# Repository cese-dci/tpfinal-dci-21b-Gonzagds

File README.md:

## Trabajo práctico final de la asignatura DCI ##
Este repositorio contiene el trabajo práctico final para la asignatura de Diseño de Circuitos Impresos de la carrera de posgrado de FIUBA.

* Autor: Gonzalo Daniel Sanchez
* Título corto del trabajo:  Programador y debugger para módulos ESP-32
* Descripción: Esta placa hace uso de un conversor USB a UART/JTAG/I2C/SPI de la empresa FTDI para implementar un grabador y debugger para módulos y kits de desarrollo de la empresa Espresiff. La placa tiene un conector para usar de grabador y otro conector para usa de debugger.
Para el grabador se configura uno de los puertos del  conversor FTDI como un puerto UART y se conectan las señales de RX y TX a la UART del módulo ESP32. Las señales de CTS y RTS se utilizan para comandar las señales de reset y programación del módulo. Esta interfaz también se puede utilizar como simple conversor USB a UART para interactuar con la consola del modulo.
El otro puerto del conversor FTDI se configura como una interfaz JTAG y se conecta directamente a las señales de JTAG del módulo Espressif.

## Licencia de este trabajo ##
XXXMENCIONAR ACÁ LA LICENCIAXXX (Editar este párrafo) 
Y además colcar el archivo de texto de la misma en el directorio raíz.
Para este TP se pide que la licencia sea de hardware abierto.
Ver la sección "What license should I use?": https://www.oshwa.org/faq/

## Estructura del TP FINAL ##

Se propone y se pide utilizar la siguiente estructura.

* doc: Toda la información sobre el circuito, principalmente de autoría o procesamiento propio. Por ejemplo:
  * Notas de ingeniería propias.
  * Notas de aplicación propias.
  * Estudios previos, estado del arte, resumen de las investigaciones.
  * Notas con cálculos.
  * Dibujos adicionales.
  * Fotos de los prototipos.
  * Presupuestos, cotizaciones.
* info: Toda la iformación recolectada, principalmente de terceros, como por ejemplo:
  * Hojas de datos.
  * Notas de aplicación.
  * Info de productos comerciales.
  * Info en internet.
* pcb: Archivos de diseño esquemático y pcb.

Dependiendo la magnitud del proyecto, tendremos más o menos información en estos directorios. 
Revisar los README.md en cada directorio para conocer las pautas de cada uno para este TP.

NOTA: El alumno puede y debe borrar de este archivo todo lo que considere necesario, por ejemplo las aclaraciones del docente y esta misma nota.

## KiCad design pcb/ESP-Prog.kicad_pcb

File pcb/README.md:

## Archivos Kicad ##

En este directorio debería ir:

* Archivos de proyecto.
* Esquemático.
* PCB.
* Modelos  3D.
* Bibliotecas de símbolos y huellas externas (si son necesarios).

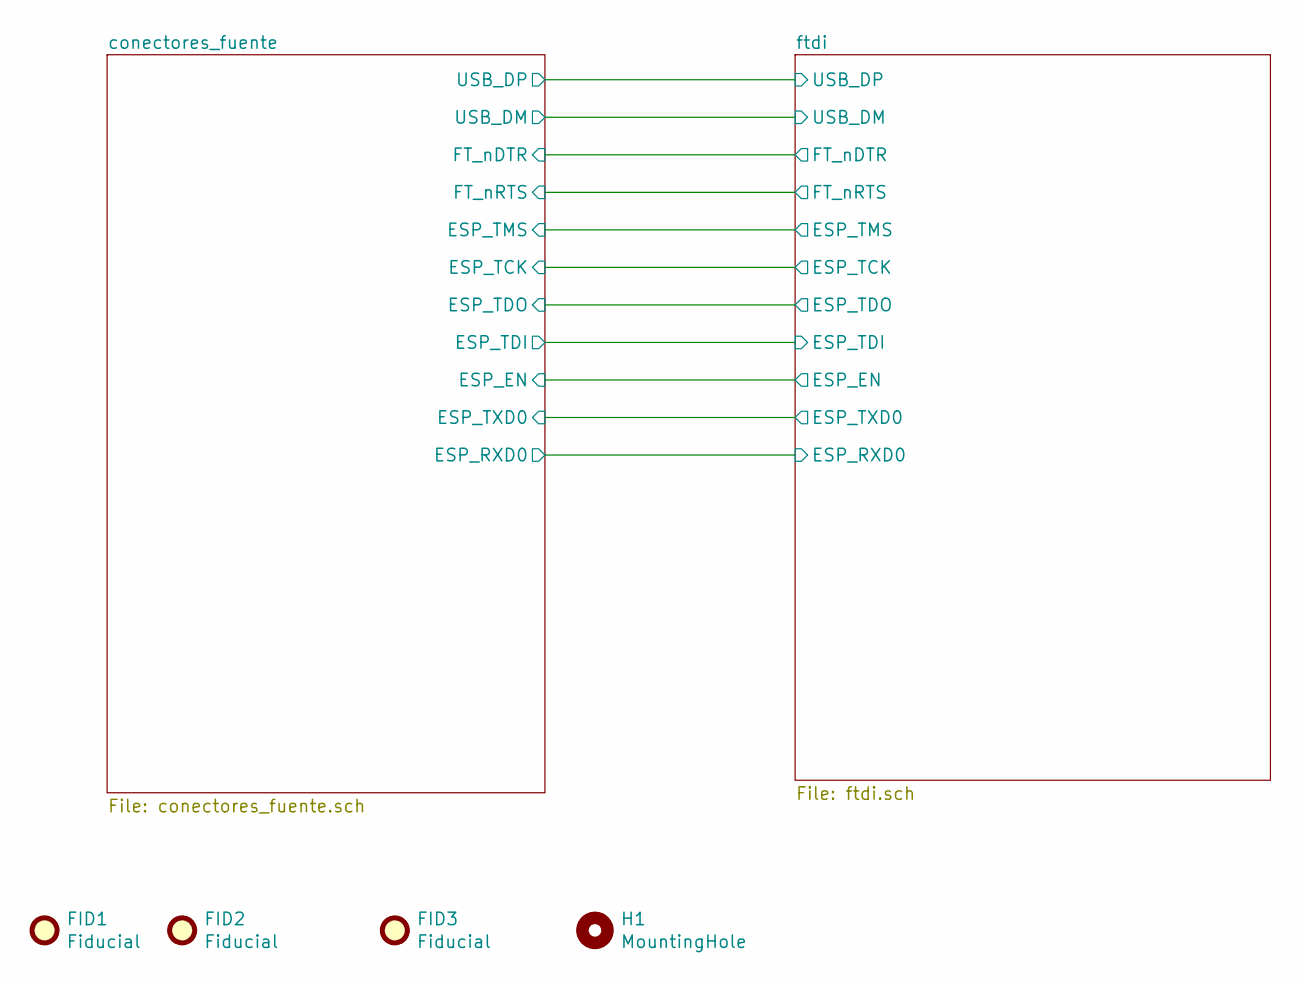
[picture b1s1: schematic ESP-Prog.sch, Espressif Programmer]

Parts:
FID1, FID2, FID3: Fiducial; Fiducial_0.5mm_Mask1mm
H1: MountingHole; MountingHole_2.5mm

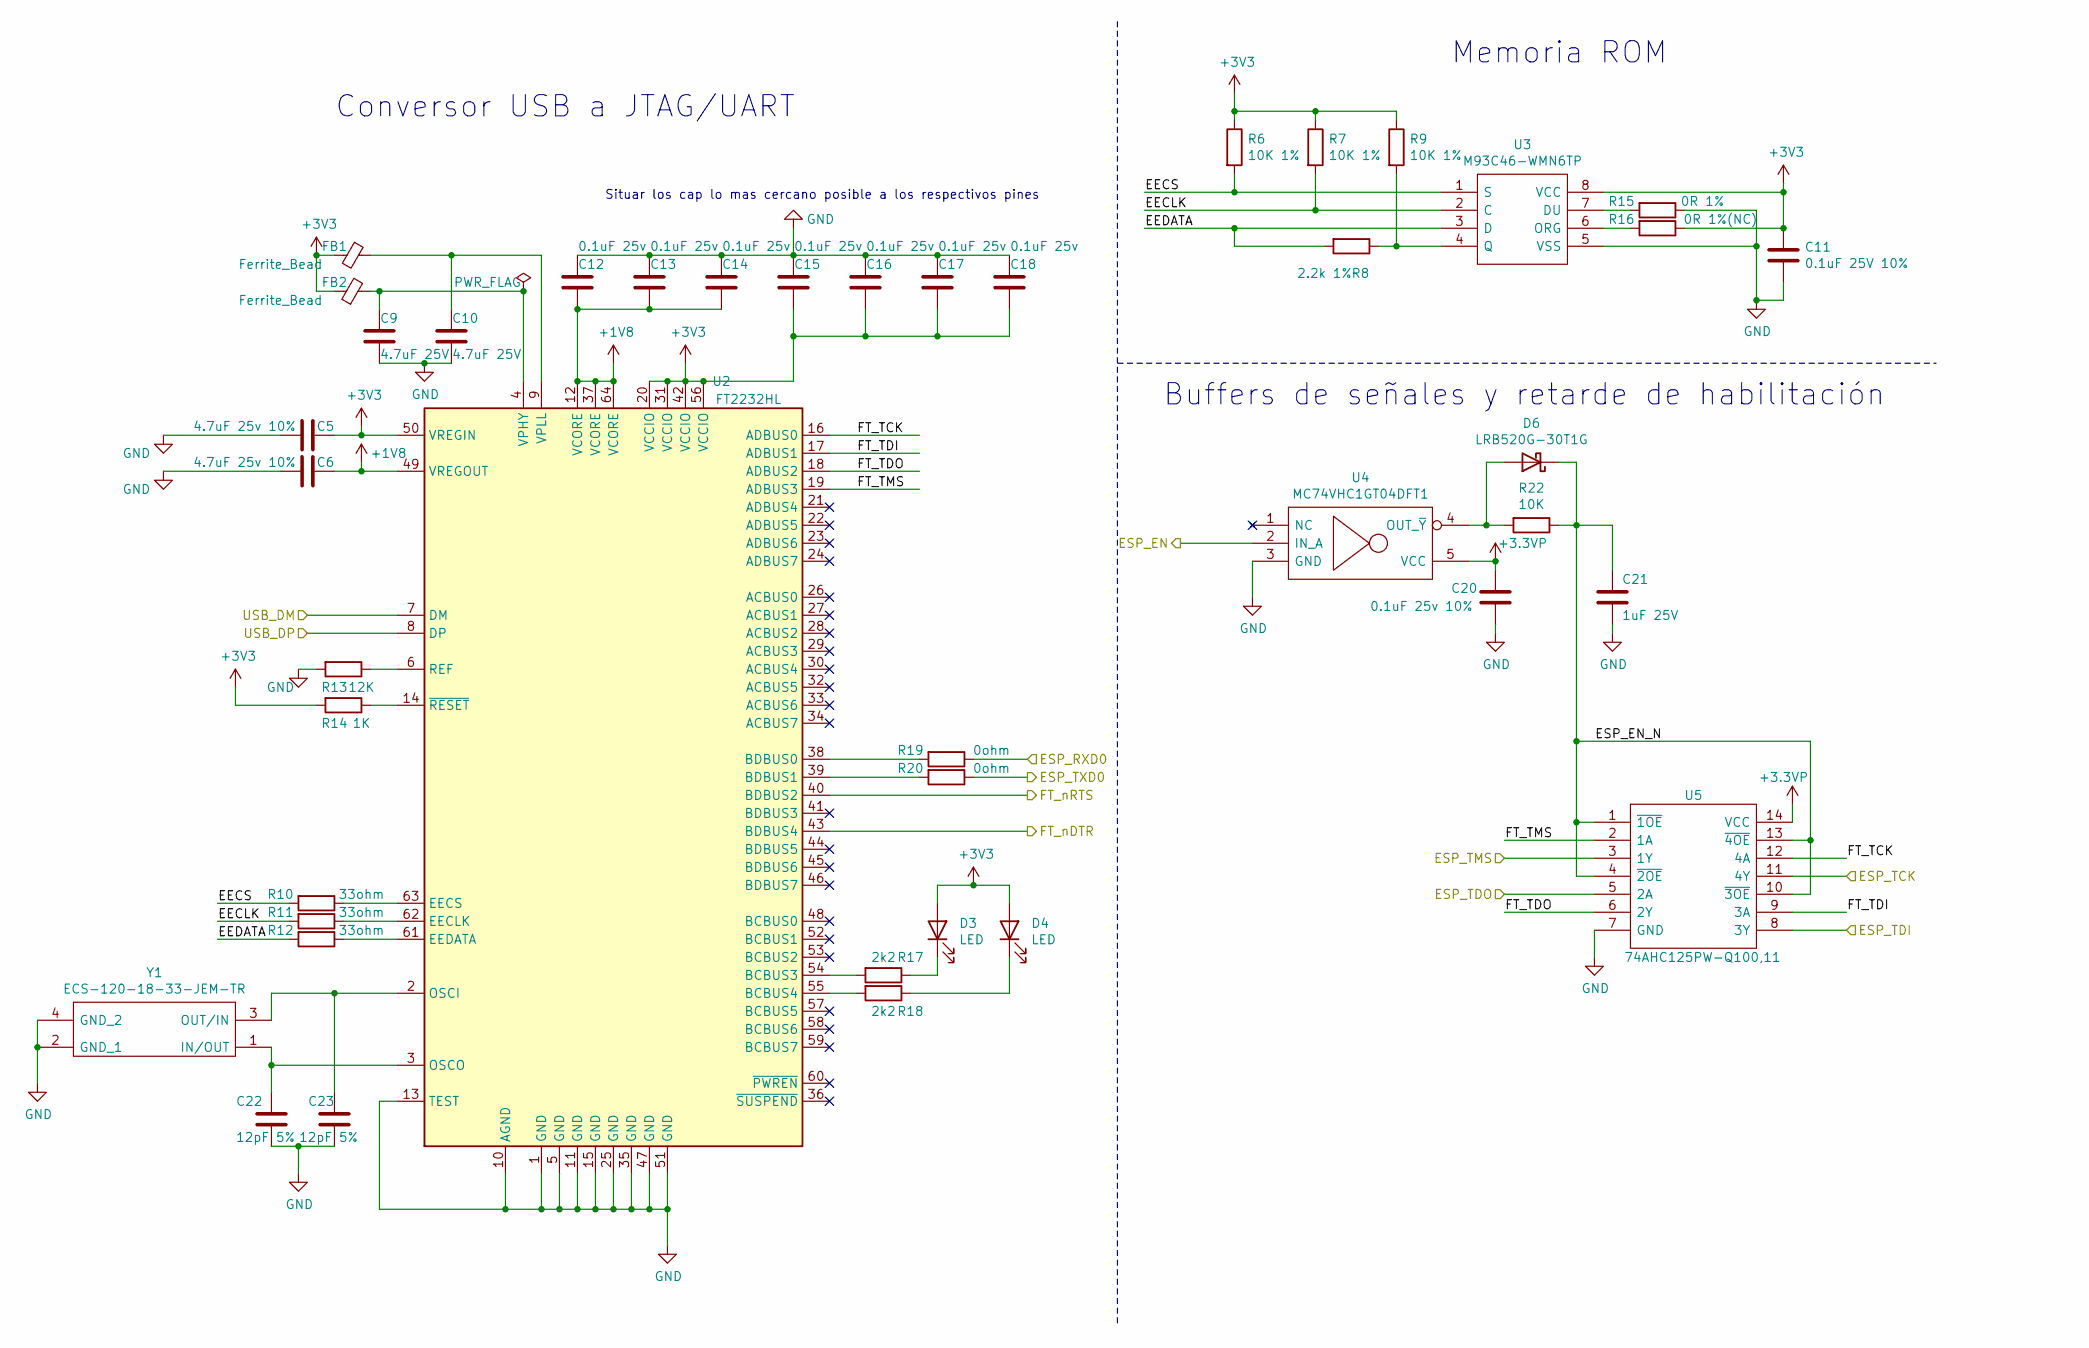
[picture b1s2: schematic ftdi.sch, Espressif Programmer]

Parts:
C5, C6: 4.7uF 25v 10%; C_0603_1608Metric
C9, C10: 4.7uF 25V; C_0603_1608Metric
C11: 0.1uF 25V 10%; C_0603_1608Metric
C12, C13, C14, C15, C16, C17, C18: 0.1uF 25v; C_0603_1608Metric
C20: 0.1uF 25v 10%; C_0603_1608Metric
C21: 1uF 25V; C_0603_1608Metric
C22, C23: 12pF 5%; C_0603_1608Metric
D3, D4: LED; LED_0603_1608Metric
D6: LRB520G-30T1G; D_0603_1608Metric
FB1, FB2: Ferrite_Bead; L_0603_1608Metric
R6, R7, R9: 10K 1%; R_0603_1608Metric
R8: 2.2k 1%; R_0603_1608Metric
R10, R11, R12: 33ohm; R_0603_1608Metric
R13: 12K; R_0603_1608Metric
R14: 1K; R_0603_1608Metric
R15: 0R 1%; R_0603_1608Metric
R16: 0R 1%(NC); R_0603_1608Metric
R17, R18: 2k2; R_0603_1608Metric
R19, R20: 0ohm; R_0603_1608Metric
R22: 10K; R_0603_1608Metric
U2: FT2232HL; LQFP-64_10x10mm_P0.5mm
U3: M93C46-WMN6TP; SOIC127P600X175-8N; Mouser Part Number 511-M93C46-WMN6TP
U4: MC74VHC1GT04DFT1; SOT65P210X110-5N; Mouser Part Number 863-MC74VHC1GT04DFT1
U5: 74AHC125PW-Q100,11; SOP65P640X110-14N; Mouser Part Number 771-74AHC125PWQ10011
Y1: ECS-120-18-33-JEM-TR; Crystal_SMD_0603-4Pin_6.0x3.5mm; Mouser Part Number 520-120-18-33-JEMT

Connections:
+1V8: C6.1, C12.2, C13.2, C14.2, U2.12 (VCORE), U2.37 (VCORE), U2.49 (VREGOUT), U2.64 (VCORE)
+3.3VP: C20.1, U4.5 (VCC), U5.14 (VCC); also elsewhere on the board
+3V3: C5.1, C11.1, C15.2, C16.2, C17.2, C18.2, D3.2 (A), D4.2 (A), FB1.2, FB2.1, R6.1, R7.1, R9.1, R14.2, R16.1, U2.20 (VCCIO), U2.31 (VCCIO), U2.42 (VCCIO), U2.50 (VREGIN), U2.56 (VCCIO), U3.8 (VCC); also elsewhere on the board
/conectores_fuente/ESP_EN: U4.2 (IN_A); also elsewhere on the board
/conectores_fuente/ESP_RXD0: R19.1; also elsewhere on the board
/conectores_fuente/ESP_TCK: U5.11 (4Y); also elsewhere on the board
/conectores_fuente/ESP_TDI: U5.8 (3Y); also elsewhere on the board
/conectores_fuente/ESP_TDO: U5.5 (2A); also elsewhere on the board
/conectores_fuente/ESP_TMS: U5.3 (1Y); also elsewhere on the board
/conectores_fuente/ESP_TXD0: R20.1; also elsewhere on the board
/conectores_fuente/FT_nDTR: U2.43 (BDBUS4); also elsewhere on the board
/conectores_fuente/FT_nRTS: U2.40 (BDBUS2); also elsewhere on the board
/conectores_fuente/USB_DM: U2.7 (DM); also elsewhere on the board
/conectores_fuente/USB_DP: U2.8 (DP); also elsewhere on the board
/ftdi/EECLK: R7.2, R11.2, U3.2 (C)
/ftdi/EECS: R6.2, R10.2, U3.1 (S)
/ftdi/EEDATA: R8.2, R12.2, U3.3 (D)
/ftdi/ESP_EN_N: C21.1, D6.1 (K), R22.1, U5.1 (~1OE), U5.4 (~2OE), U5.10 (~3OE), U5.13 (~4OE)
/ftdi/FT_TCK: U2.16 (ADBUS0), U5.12 (4A)
/ftdi/FT_TDI: U2.17 (ADBUS1), U5.9 (3A)
/ftdi/FT_TDO: U2.18 (ADBUS2), U5.6 (2Y)
/ftdi/FT_TMS: U2.19 (ADBUS3), U5.2 (1A)
GND: C5.2, C6.2, C9.2, C10.2, C11.2, C12.1, C13.1, C14.1, C15.1, C16.1, C17.1, C18.1, C20.2, C21.2, C22.2, C23.2, R13.2, R15.1, U2.1 (GND), U2.5 (GND), U2.10 (AGND), U2.11 (GND), U2.13 (TEST), U2.15 (GND), U2.25 (GND), U2.35 (GND), U2.47 (GND), U2.51 (GND), U3.5 (VSS), U4.3 (GND), U5.7 (GND), Y1.2 (GND_1), Y1.4 (GND_2); also elsewhere on the board
unnamed: C9.1, FB2.2, U2.4 (VPHY)
unnamed: C10.1, FB1.1, U2.9 (VPLL)
unnamed: C22.1, U2.3 (OSCO), Y1.1 (IN/OUT)
unnamed: C23.1, U2.2 (OSCI), Y1.3 (OUT/IN)
unnamed: D3.1 (K), R17.1
unnamed: D4.1 (K), R18.1
unnamed: D6.2 (A), R22.2, U4.4 (OUT_~Y)
unnamed: R8.1, R9.2, U3.4 (Q)
unnamed: R10.1, U2.63 (EECS)
unnamed: R11.1, U2.62 (EECLK)
unnamed: R12.1, U2.61 (EEDATA)
unnamed: R13.1, U2.6 (REF)
unnamed: R14.1, U2.14 (~RESET)
unnamed: R15.2, U3.7 (DU)
unnamed: R16.2, U3.6 (ORG)
unnamed: R17.2, U2.54 (BCBUS3)
unnamed: R18.2, U2.55 (BCBUS4)
unnamed: R19.2, U2.38 (BDBUS0)
unnamed: R20.2, U2.39 (BDBUS1)

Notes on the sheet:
Situar los cap lo mas cercano posible a los respectivos pines
Conversor USB a JTAG/UART
Memoria ROM
Buffers de señales y retarde de habilitación

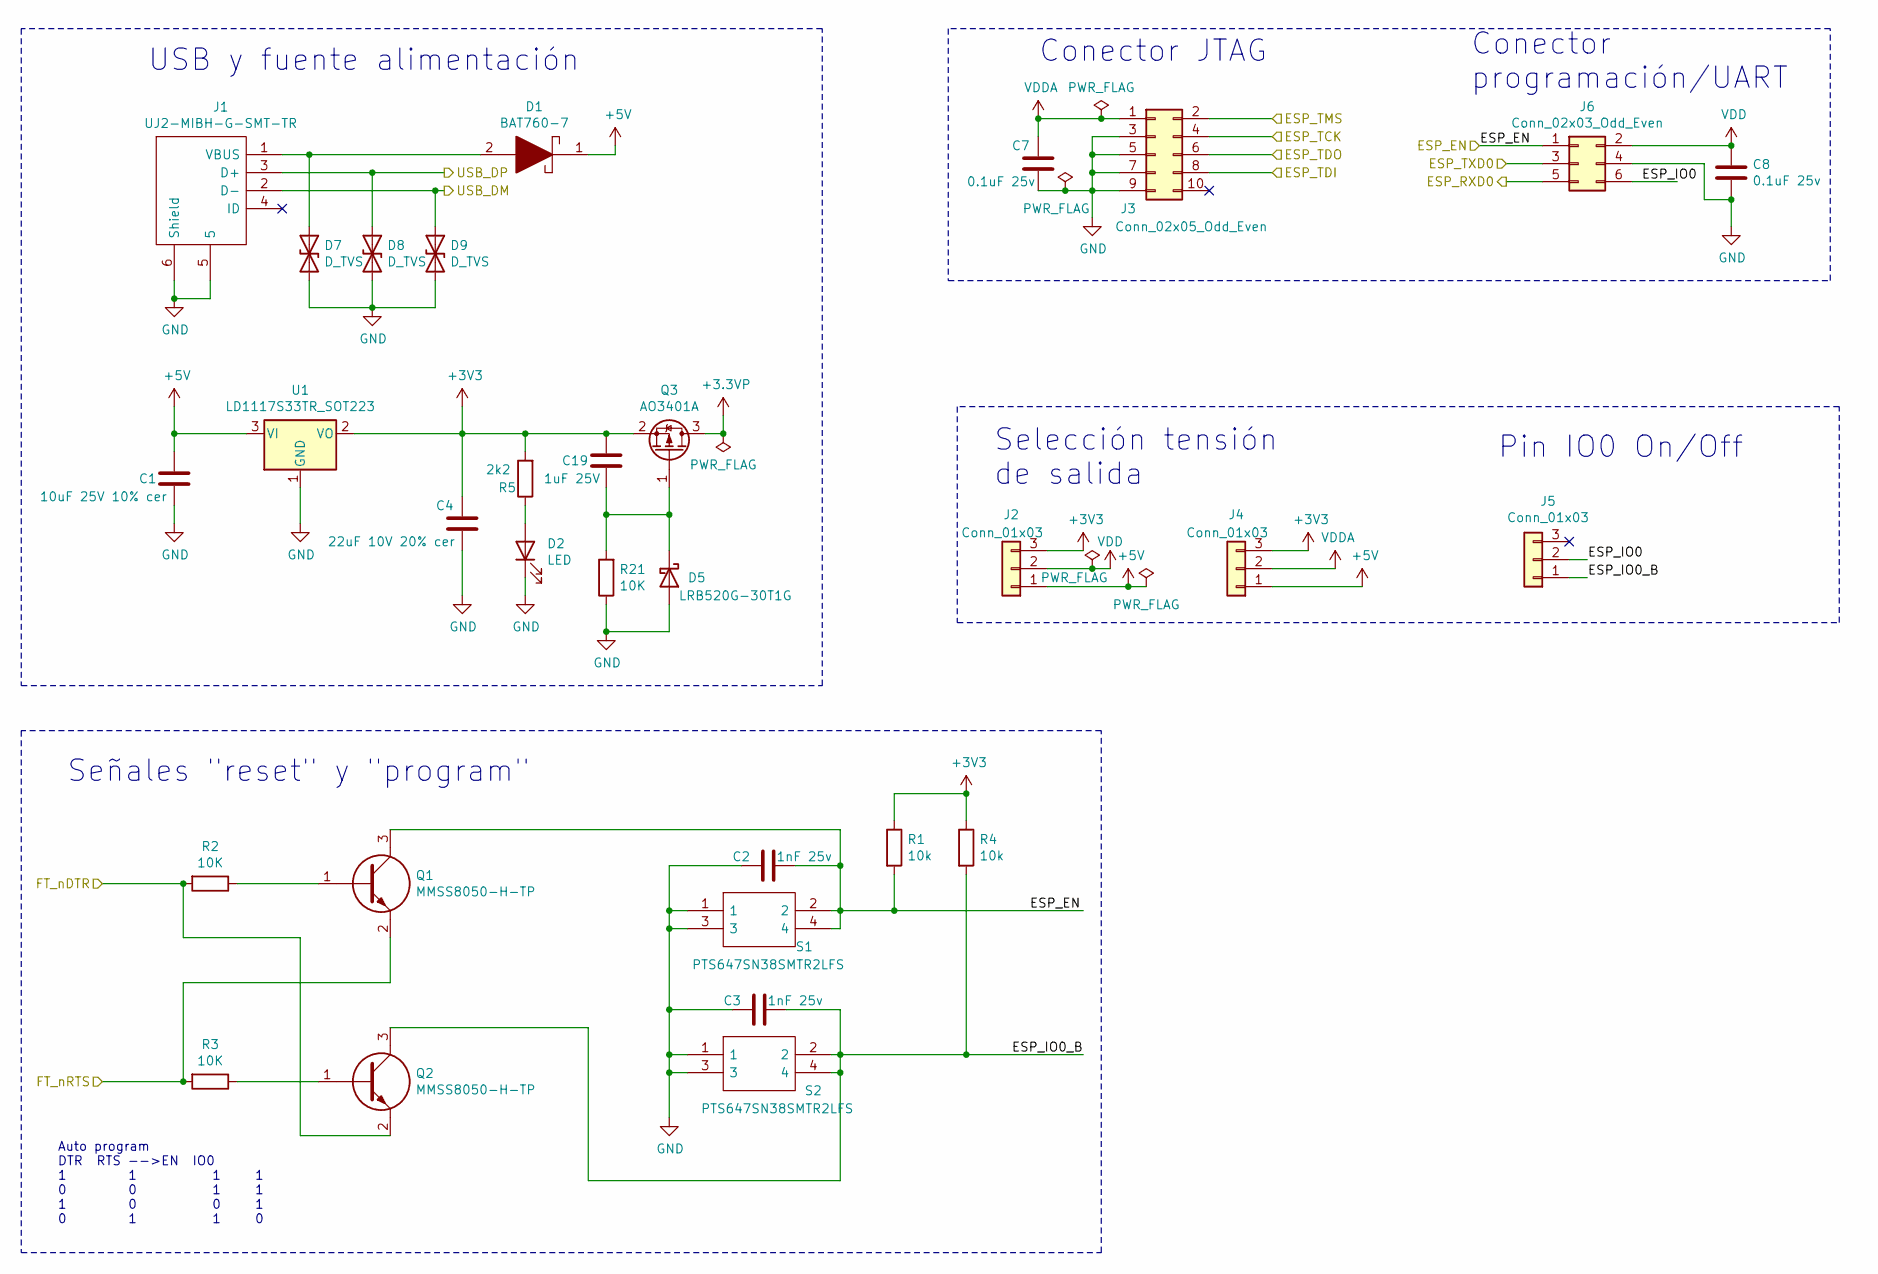
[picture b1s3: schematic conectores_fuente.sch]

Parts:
C1: 10uF 25V 10% cer; C_0603_1608Metric
C2, C3: 1nF 25v; C_0603_1608Metric
C4: 22uF 10V 20% cer; C_0603_1608Metric
C7, C8: 0.1uF 25v; C_0603_1608Metric
C19: 1uF 25V; C_0603_1608Metric
D1: BAT760-7; D_SOD-323; Mouser Part Number 621-BAT760-7
D2: LED; LED_0603_1608Metric
D5: LRB520G-30T1G; D_0603_1608Metric
D7, D8, D9: D_TVS; D_SOD-523
J1: UJ2-MIBH-G-SMT-TR; UJ2MIBHGSMTTR; Mouser Part Number 490-UJ2-MIBH-G-SMTTR
J2, J4, J5: Conn_01x03; PinHeader_1x03_P2.54mm_Vertical
J3: Conn_02x05_Odd_Even; PinHeader_2x05_P1.27mm_Vertical_SMD
J6: Conn_02x03_Odd_Even; PinHeader_2x03_P1.27mm_Vertical_SMD
Q1, Q2: MMSS8050-H-TP; SI2305TP; Mouser Part Number 833-MMSS8050-H-TP
Q3: AO3401A; SOT-23
R1, R4: 10k; R_0603_1608Metric
R2, R3, R21: 10K; R_0603_1608Metric
R5: 2k2; R_0603_1608Metric
S1, S2: PTS647SN38SMTR2LFS; PTS647SM38SMTR2LFS; Mouser Part Number 611-PTS647SN38SMTR2L
U1: LD1117S33TR_SOT223; SOT-223-3_TabPin2

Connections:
+3.3VP: Q3.3 (D); also elsewhere on the board
+3V3: C4.1, C19.1, J2.3, J4.3, Q3.2 (S), R1.1, R4.1, R5.2, U1.2 (VO); also elsewhere on the board
+5V: C1.1, D1.1, J2.1, J4.1, U1.3 (VI)
/conectores_fuente/ESP_EN: C2.1, J6.1, Q1.3, R1.2, S1.2, S1.4; also elsewhere on the board
/conectores_fuente/ESP_IO0: J5.2, J6.6
/conectores_fuente/ESP_IO0_B: C3.1, J5.1, Q2.3, R4.2, S2.2, S2.4
/conectores_fuente/ESP_RXD0: J6.5; also elsewhere on the board
/conectores_fuente/ESP_TCK: J3.4; also elsewhere on the board
/conectores_fuente/ESP_TDI: J3.8; also elsewhere on the board
/conectores_fuente/ESP_TDO: J3.6; also elsewhere on the board
/conectores_fuente/ESP_TMS: J3.2; also elsewhere on the board
/conectores_fuente/ESP_TXD0: J6.3; also elsewhere on the board
/conectores_fuente/FT_nDTR: Q2.2, R2.2; also elsewhere on the board
/conectores_fuente/FT_nRTS: Q1.2, R3.2; also elsewhere on the board
/conectores_fuente/USB_DM: D9.1 (A1), J1.2 (D-); also elsewhere on the board
/conectores_fuente/USB_DP: D8.1 (A1), J1.3 (D+); also elsewhere on the board
GND: C1.2, C2.2, C3.2, C4.2, C7.2, C8.2, D2.1 (K), D5.2 (A), D7.2 (A2), D8.2 (A2), D9.2 (A2), J1.5, J1.6 (Shield), J3.3, J3.5, J3.7, J3.9, J6.4, R21.1, S1.1, S1.3, S2.1, S2.3, U1.1 (GND); also elsewhere on the board
unnamed: C19.2, D5.1 (K), Q3.1 (G), R21.2
unnamed: D1.2, D7.1 (A1), J1.1 (VBUS)
unnamed: D2.2 (A), R5.1
unnamed: Q1.1, R2.1
unnamed: Q2.1, R3.1
VDD: C8.1, J2.2, J6.2
VDDA: C7.1, J3.1, J4.2

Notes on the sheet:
Auto program DTR RTS -->EN IO0 1 1 1 1 0 0 1 1 1 0 0 1 0 1 1 0
Conector JTAG
Conector programación/UART
Selección tensión de salida
Pin IO0 On/Off
USB y fuente alimentación
Señales "reset" y "program"

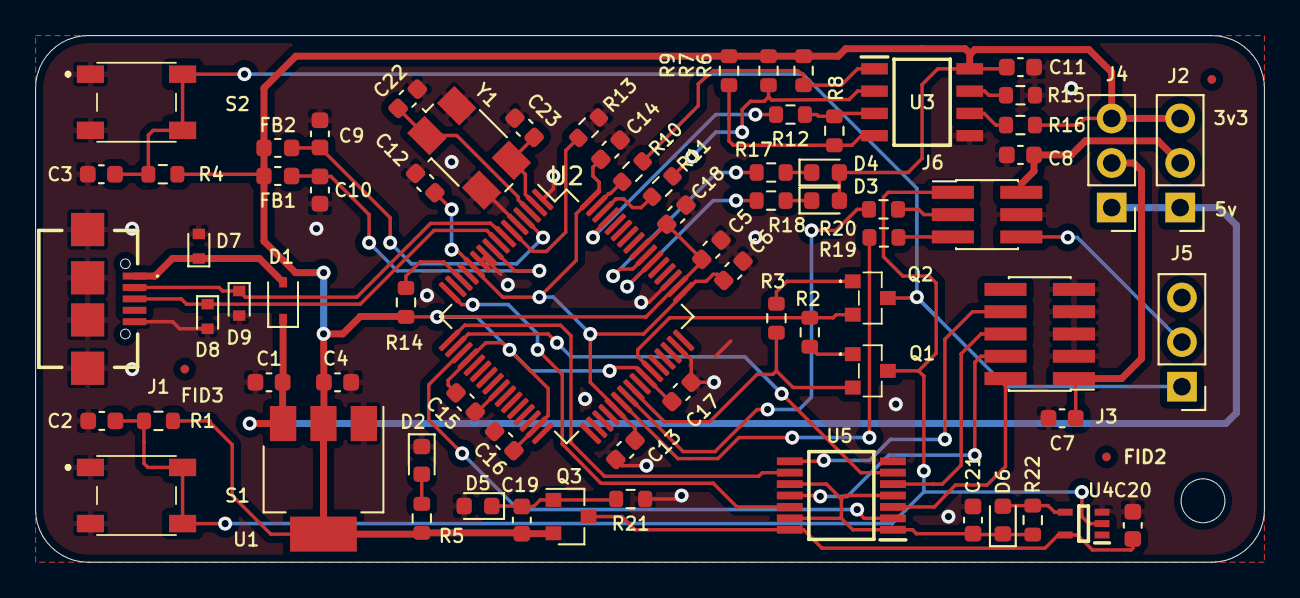
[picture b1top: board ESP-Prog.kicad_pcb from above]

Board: 2 copper layers, 70.0 x 30.0 mm, 77 parts (0 on the bottom side), 52 nets.

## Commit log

2021-07-26 primer commit
2021-08-03 primer versión terminada del esquemático
2021-08-10 - se agregan todos los footprints
2021-08-14 - Se agregan hojas de datos e información del proyecto.
2021-08-15 se agrega archivo git ignore
2021-08-15 se agrega información del proyecto, se completan archivos md y se agregan hojas de datos
2021-08-15 se completa readme.md
2021-08-15 probando de commitear con token
2021-08-15 correcciones al esquematico y avances en posicionamiento de pcb
2021-08-16 - Rpimer propuesta posicionamiento
2021-08-16 - Se modifica el esquemático para respetar la estructura gerarquica
2021-08-16 se agrega estructura gerarquica
2021-08-17 se agregan notas aclaratorias a los esquemáticos
2021-08-20 avances en el pcb y correcciones al esquematico
2021-08-21 Primer versión ruteo terminada
2021-08-21 Primer versión ruteo terminada. se agregan archivos faltantes
2021-08-21 revisiones
